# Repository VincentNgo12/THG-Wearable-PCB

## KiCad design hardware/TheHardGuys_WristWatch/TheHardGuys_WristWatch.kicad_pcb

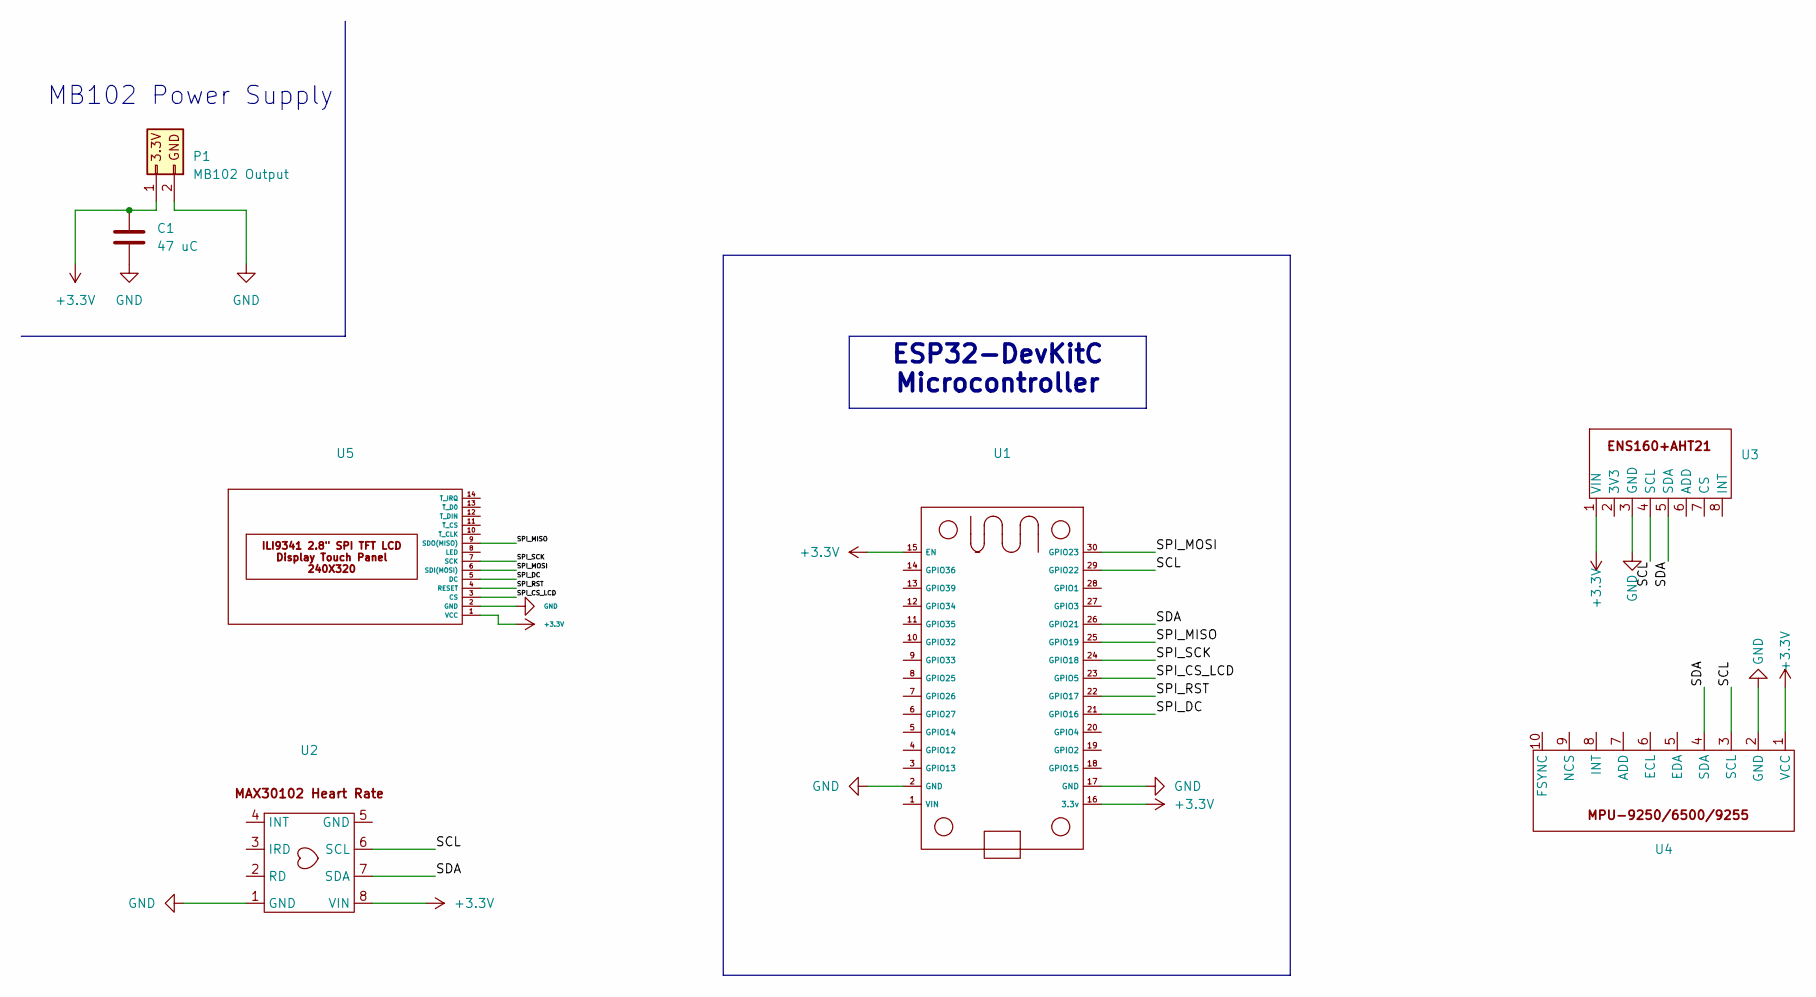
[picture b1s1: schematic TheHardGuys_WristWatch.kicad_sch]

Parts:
C1: 47 uC; CP_Radial_D6.3mm_P2.50mm
P1: MB102 Output; MB102_Breadboard_Power_Module
U1: ESP32_30pin
U2: MAX30102 Heart Rate_Pulse Sensor
U3: ENS160+AHT21_Environmental_Sensor
U4: MPU6500_IMU
U5: ILI9341_2.8__SPI_TFT_LCD

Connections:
+3.3V: C1.1, P1.1 (3.3V), P1.3 (3.3V), U1.15 (EN), U1.16 (3.3v), U2.8 (VIN), U3.1 (VIN), U4.1 (VCC), U5.1 (VCC); also elsewhere on the board
/SCL: U1.29 (GPIO22), U2.6 (SCL), U3.4 (SCL), U4.3 (SCL)
/SDA: U1.26 (GPIO21), U2.7 (SDA), U3.5 (SDA), U4.4 (SDA)
/SPI_CS_LCD: U1.23 (GPIO5), U5.3 (CS)
/SPI_DC: U1.21 (GPIO16), U5.5 (DC)
/SPI_MISO: U1.25 (GPIO19), U5.9 (SDO(MISO))
/SPI_MOSI: U1.30 (GPIO23), U5.6 (SDI(MOSI))
/SPI_RST: U1.22 (GPIO17), U5.4 (RESET)
/SPI_SCK: U1.24 (GPIO18), U5.7 (SCK)
GND: C1.2, P1.2 (GND), P1.4 (GND), U1.2 (GND), U1.17 (GND), U2.1 (GND), U3.3 (GND), U4.2 (GND), U5.2 (GND); also elsewhere on the board

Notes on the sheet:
MB102 Power Supply
ESP32-DevKitC Microcontroller

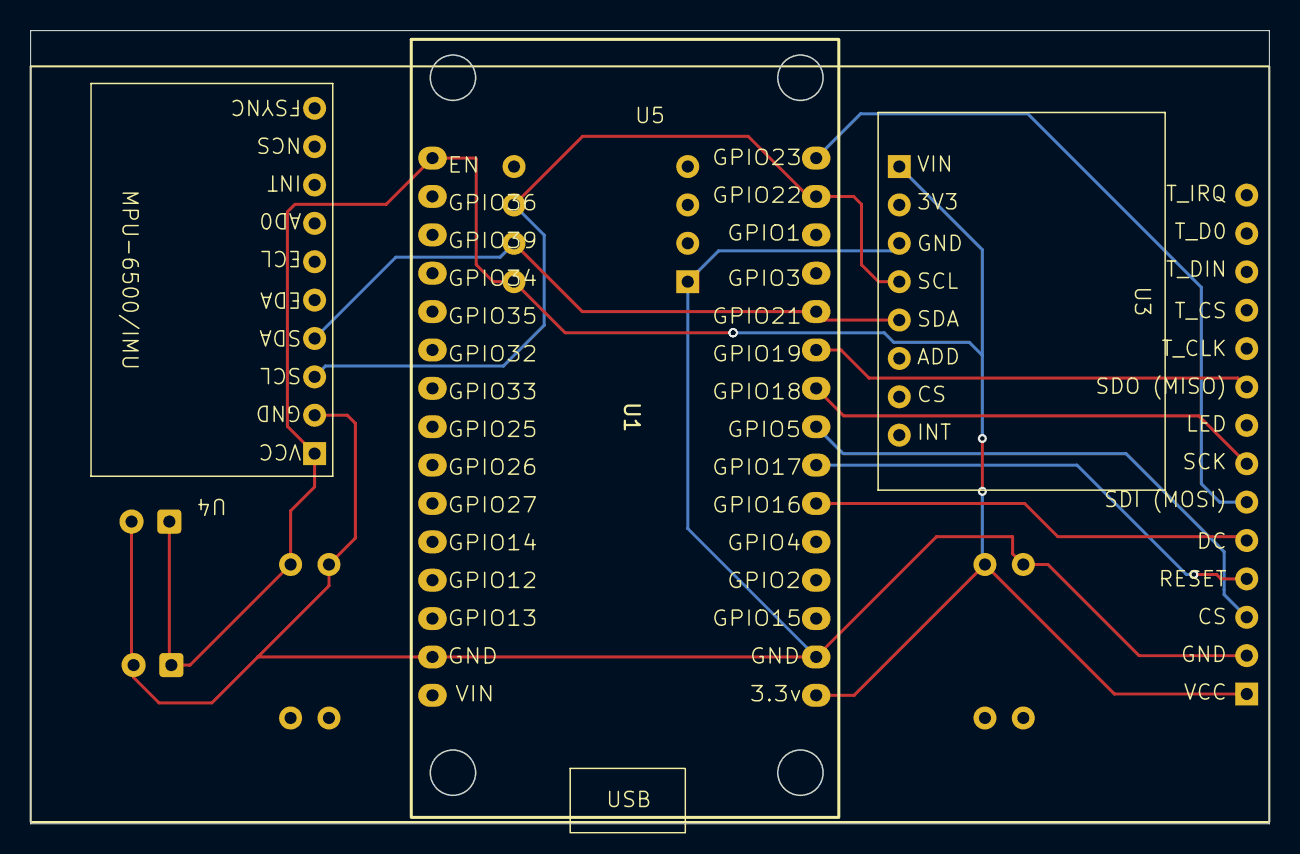
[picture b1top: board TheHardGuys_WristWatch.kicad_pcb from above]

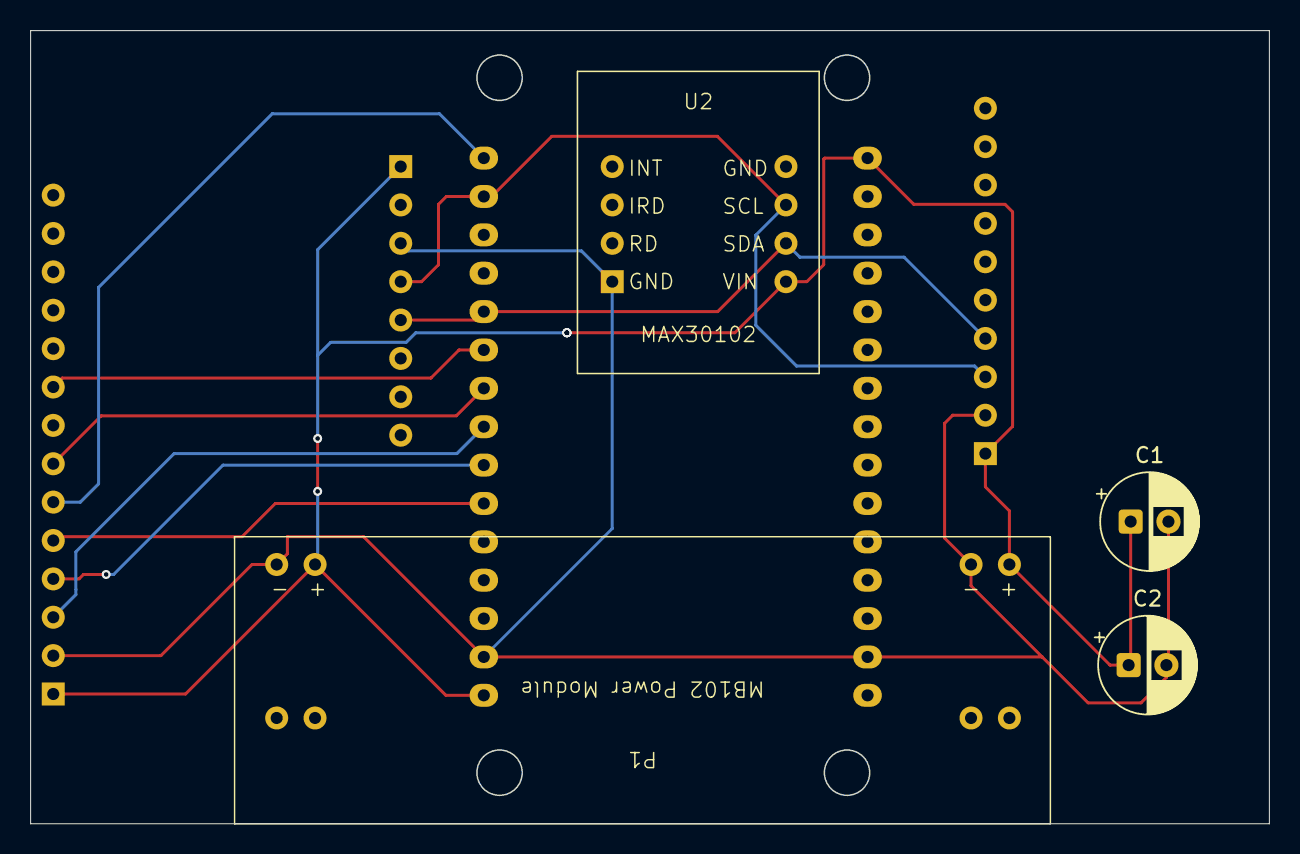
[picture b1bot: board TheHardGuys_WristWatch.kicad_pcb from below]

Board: 2 copper layers, 82.0 x 52.5 mm, 8 parts (4 on the bottom side), 10 nets.

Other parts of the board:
C2: 47 uC; CP_Radial_D6.3mm_P2.50mm

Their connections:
+3.3V: C2.1; also elsewhere on the board
GND: C2.2; also elsewhere on the board

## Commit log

2026-01-21 Create KiCad project files
2026-02-05 Create more custom symbols and footprints.
2026-02-07 Finalize Custom Symbols and Footprints
2026-02-11 Work on Schematic & Add MB102 Footprint
2026-02-12 Basic PCB Design Done First Iteration. Silk screen not well setup. Zero errors, 40 Warnings.
2026-02-13 Added ESP32 Feather V2 Symbol and Footprint
2026-02-13 Small Changes to Schematic
